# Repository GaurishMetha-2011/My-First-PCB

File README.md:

# My-First-PCB
PCB For Obstacle Avoidance Card With Arduino Nano, Ultrasonic Sensor &amp; LED
# My First Obstacle Avoidance PCB Layout

### 3D Board Preview

**Top View:**

**Corner View:**

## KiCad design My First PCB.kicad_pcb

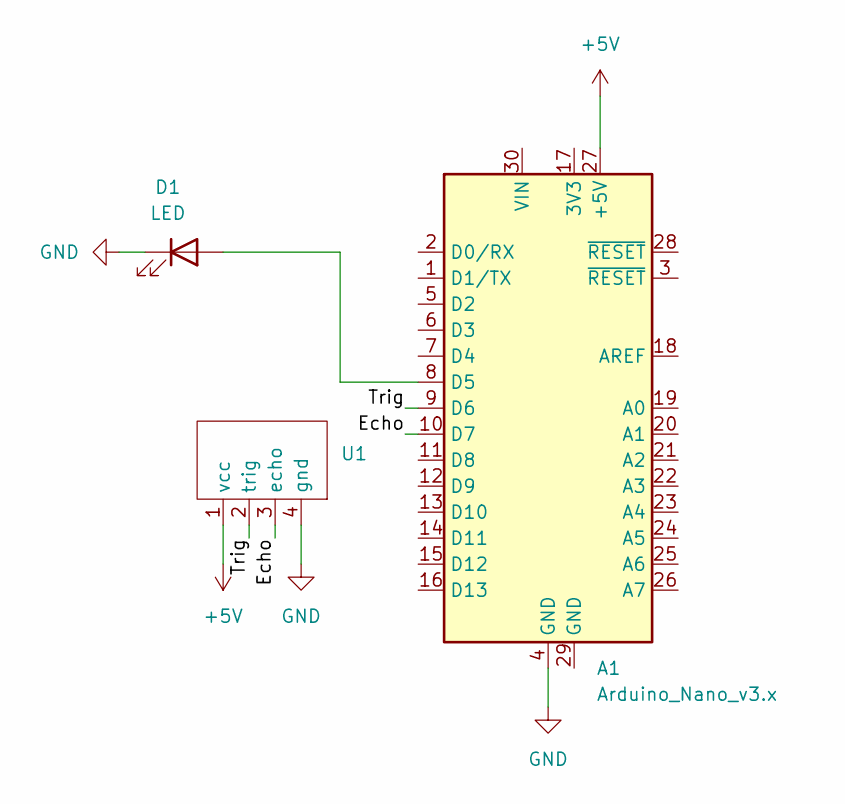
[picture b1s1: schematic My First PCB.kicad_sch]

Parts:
A1: Arduino_Nano_v3.x; Arduino_Nano
D1: LED; LED_D4.0mm
U1: Ultrasonic Sensor

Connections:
+5V: A1.27 (+5V), U1.1 (vcc)
/Echo: A1.10 (D7), U1.3 (echo)
/Trig: A1.9 (D6), U1.2 (trig)
GND: A1.4 (GND), D1.1 (K), U1.4 (gnd)
unnamed: A1.8 (D5), D1.2 (A)

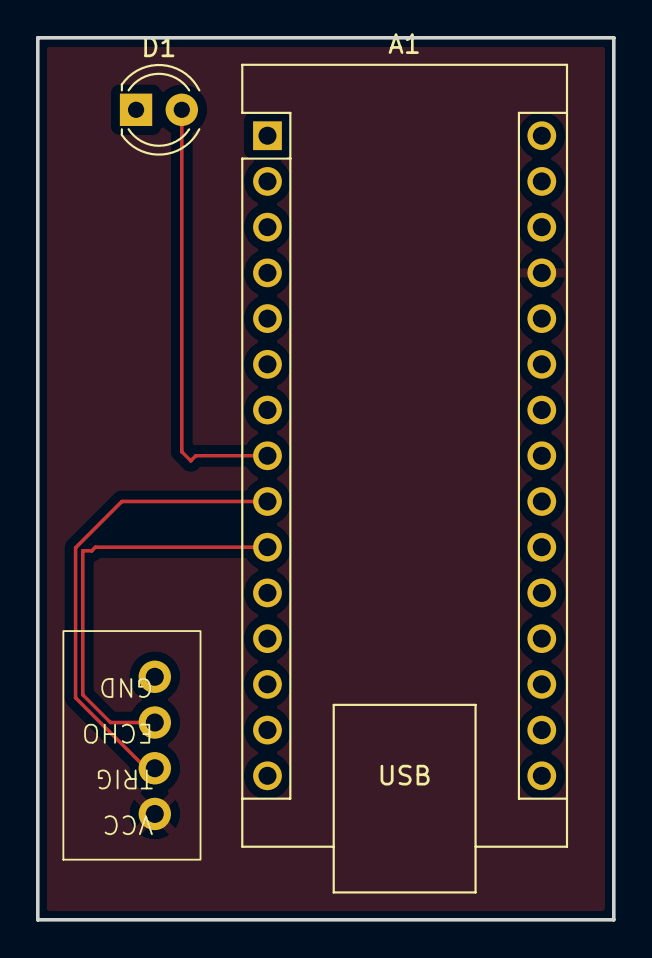
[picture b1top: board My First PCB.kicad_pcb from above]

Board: 2 copper layers, 32.0 x 49.0 mm, 3 parts (0 on the bottom side), 5 nets.
